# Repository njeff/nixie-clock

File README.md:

# Nixie Clock
This repository contains the KiCAD files for the PCB and the Atmel Studio files for the code.

If you plan on recreating this, I recommend changing the PCB design to use all SMD components and paying attention to high voltage clearance.

[Instructables](https://www.instructables.com/id/SMD-Nixie-Clock/) write up for this project.

Uses the following libraries:
- Zak Kemble's [millis](https://github.com/zkemble/millis) library
- akafugu's [DS3231](https://github.com/akafugu/ds_rtc_lib) RTC library

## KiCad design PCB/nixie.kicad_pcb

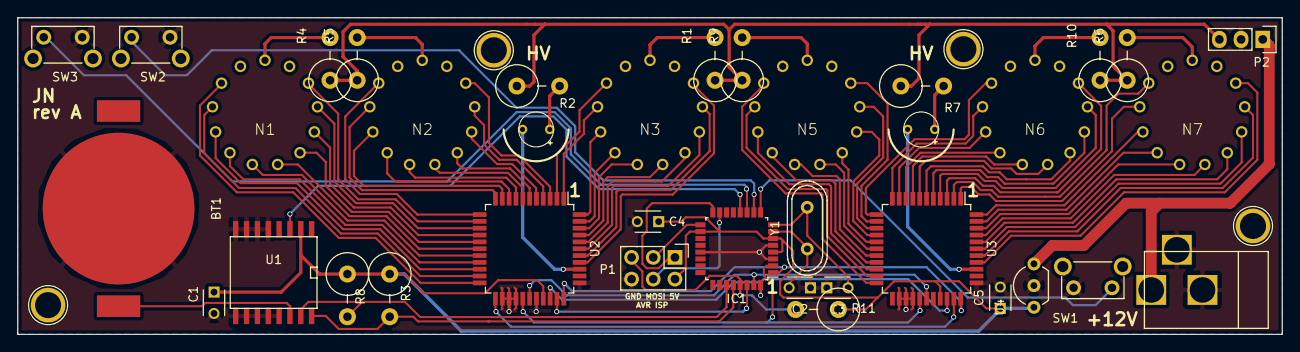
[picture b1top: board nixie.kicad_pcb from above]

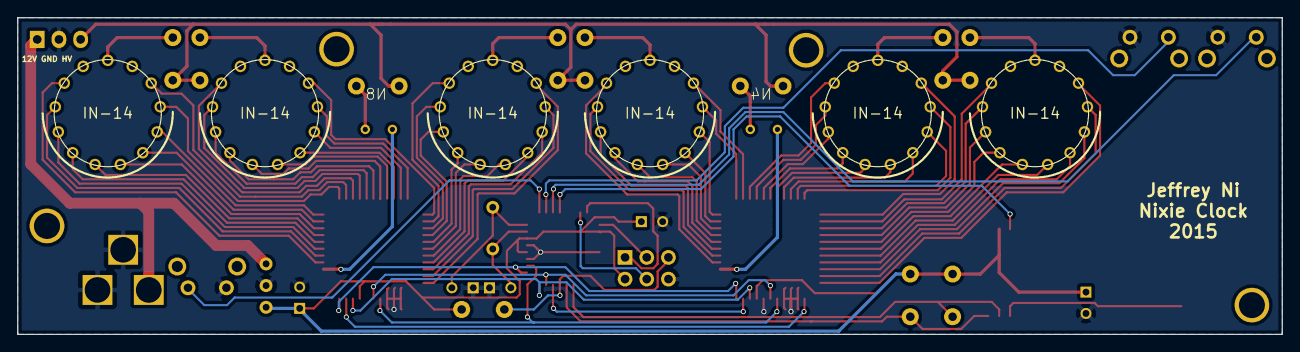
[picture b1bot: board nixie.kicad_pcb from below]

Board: 2 copper layers, 148.1 x 37.1 mm, 37 parts (6 on the bottom side), 93 nets.

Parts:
BT1: CR2032
C1, C4, C5: 0.1uF; C_Disc_D3_P2.5
C2, C3: 22pF; C_Disc_D3_P2.5
CON1: BARREL_JACK
IC1: ATMEGA328P-M; LQFP-32_7x7mm_Pitch0.8mm
N1, N2, N3, N5, N6, N7: IN-14; russian-nixies-IN-14
N4, N8: IN-3; russian-nixies-IN-3
P1: CONN_02X03; Pin_Header_Straight_2x03
P2: CONN_01X03; Pin_Header_Straight_1x03
R1, R4, R5, R6, R9, R10: 27K; Resistor_Vertical_RM5mm
R2, R7: 100K; Resistor_Vertical_RM5mm
R3, R8: 4K7; Resistor_Vertical_RM5mm
R11: 10K; Resistor_Vertical_RM5mm
SW1, SW2, SW3: SW_PUSH; SW_Tactile_SPST_Angled
U1: DS3231N; SO-16-L
U2, U3: HV5622; LQFP-44_10x10mm_Pitch0.8mm
U4: 78L05; TO-92_Inline_Wide
Y1: Crystal; Crystal_HC49-U_Vertical

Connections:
+5V: C1.1, C4.1, C5.1, IC1.4, IC1.6, IC1.18, P1.2, R3.1, R8.1, R11.1, U1.2, U2.30, U3.30, U4.1
+12V: CON1.1, P2.1, U4.3
GND: BT1.2, C1.2, C2.1, C3.1, C4.2, C5.2, CON1.2, CON1.3, IC1.3, IC1.5, IC1.21, P1.6, P2.2, SW1.2, SW2.2, SW3.2, U1.5, U1.6, U1.7, U1.8, U1.9, U1.10, U1.11, U1.12, U1.13, U2.24, U2.25, U2.26, U2.29, U2.34, U3.24, U3.25, U3.26, U3.29, U3.34, U4.2
HT: P2.3, R1.1, R2.1, R4.1, R5.1, R6.1, R7.1, R9.1, R10.1
unnamed: BT1.1, U1.14
unnamed: C2.2, IC1.7, Y1.1
unnamed: C3.2, IC1.8, Y1.2
unnamed: IC1.1, U2.33, U3.33
unnamed: IC1.2, U2.27, U3.27
unnamed: IC1.9, SW1.1
unnamed: IC1.10, SW2.1
unnamed: IC1.11, SW3.1
unnamed: IC1.12, U1.3
unnamed: IC1.15, P1.4
unnamed: IC1.16, P1.1
unnamed: IC1.17, P1.3
unnamed: IC1.27, R8.2, U1.15
unnamed: IC1.28, R3.2, U1.16
unnamed: IC1.29, P1.5, R11.2
unnamed: IC1.30, U2.32
unnamed: IC1.31, U2.28, U3.28
unnamed: IC1.32, U2.31, U3.31
unnamed: N1.0, U2.13
unnamed: N1.1, U2.22
unnamed: N1.2, U2.21
unnamed: N1.3, U2.20
unnamed: N1.4, U2.19
unnamed: N1.5, U2.18
unnamed: N1.6, U2.17
unnamed: N1.7, U2.16
unnamed: N1.8, U2.15
unnamed: N1.9, U2.14
unnamed: N1.A, R4.2
unnamed: N2.0, U2.3
unnamed: N2.1, U2.12
unnamed: N2.2, U2.11
unnamed: N2.3, U2.10
unnamed: N2.4, U2.9
unnamed: N2.5, U2.8
unnamed: N2.6, U2.7
unnamed: N2.7, U2.6
unnamed: N2.8, U2.5
unnamed: N2.9, U2.4
unnamed: N2.A, R5.2
unnamed: N3.0, U2.37
unnamed: N3.1, U2.2
unnamed: N3.2, U2.1
unnamed: N3.3, U2.44
unnamed: N3.4, U2.43
unnamed: N3.5, U2.42
unnamed: N3.6, U2.41
unnamed: N3.7, U2.40
unnamed: N3.8, U2.39
unnamed: N3.9, U2.38
unnamed: N3.A, R1.2
unnamed: N4.A, R2.2
unnamed: N4.K, U2.36
unnamed: N5.0, U3.13
unnamed: N5.1, U3.22
unnamed: N5.2, U3.21
unnamed: N5.3, U3.20
unnamed: N5.4, U3.19
unnamed: N5.5, U3.18
unnamed: N5.6, U3.17
unnamed: N5.7, U3.16
unnamed: N5.8, U3.15
unnamed: N5.9, U3.14
unnamed: N5.A, R9.2
unnamed: N6.0, U3.3
unnamed: N6.1, U3.12
unnamed: N6.2, U3.11
unnamed: N6.3, U3.10
unnamed: N6.4, U3.9
unnamed: N6.5, U3.8
unnamed: N6.6, U3.7
unnamed: N6.7, U3.6
unnamed: N6.8, U3.5
unnamed: N6.9, U3.4
unnamed: N6.A, R10.2
unnamed: N7.0, U3.37
unnamed: N7.1, U3.2
unnamed: N7.2, U3.1
unnamed: N7.3, U3.44
unnamed: N7.4, U3.43
unnamed: N7.5, U3.42
unnamed: N7.6, U3.41
unnamed: N7.7, U3.40
unnamed: N7.8, U3.39
unnamed: N7.9, U3.38
unnamed: N7.A, R6.2
unnamed: N8.A, R7.2
unnamed: N8.K, U3.36
unnamed: U2.23, U3.32

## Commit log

2016-03-03 Removed binaries
2016-04-14 Buttons now can change the time; added rudimentary timer support
2020-05-27 README update and indentation
